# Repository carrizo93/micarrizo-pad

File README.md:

# micarrizo pad
 A macropad made using the Kailh Big Switch.

PCB front view:

PCB back view:

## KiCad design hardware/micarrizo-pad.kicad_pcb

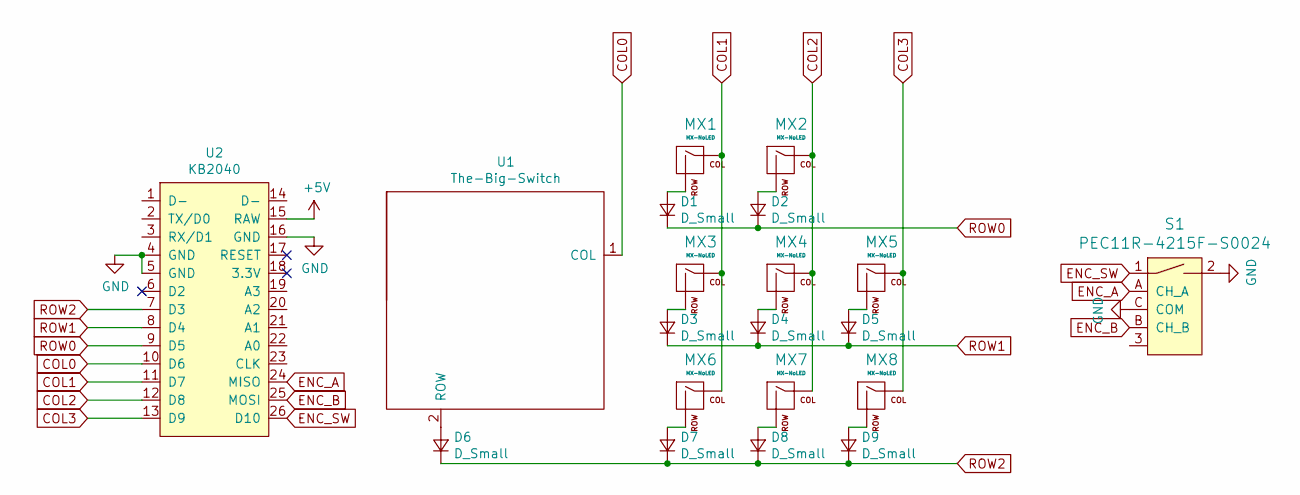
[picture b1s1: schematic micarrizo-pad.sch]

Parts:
D1, D2, D3, D4, D5, D6, D7, D8, D9: D_Small; D_SOD-123
MX1, MX2, MX3, MX4, MX5, MX6, MX7, MX8: MX-NoLED; MX-1U-NoLED
S1: PEC11R-4215F-S0024; Rotary_Encoder_Switched_PEC11R; MPN PEC11R-4215F-S0024; Digi-Key_PN PEC11R-4215F-S0024-ND
U1: The-Big-Switch; The Big Switch
U2: KB2040

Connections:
+5V: U2.15 (RAW)
COL0: U1.1 (COL), U2.10 (D6)
COL1: MX1.1 (COL), MX3.1 (COL), MX6.1 (COL), U2.11 (D7)
COL2: MX2.1 (COL), MX4.1 (COL), MX7.1 (COL), U2.12 (D8)
COL3: MX5.1 (COL), MX8.1 (COL), U2.13 (D9)
ENC_A: S1.A (CH_A), U2.24 (MISO)
ENC_B: S1.B (CH_B), U2.25 (MOSI)
ENC_SW: S1.1, U2.26 (D10)
GND: S1.2, S1.C (COM), U2.4 (GND), U2.5 (GND), U2.16 (GND)
unnamed: D1.2 (A), MX1.2 (ROW)
unnamed: D2.2 (A), MX2.2 (ROW)
unnamed: D3.2 (A), MX3.2 (ROW)
unnamed: D4.2 (A), MX4.2 (ROW)
unnamed: D5.2 (A), MX5.2 (ROW)
unnamed: D6.2 (A), U1.2 (ROW)
unnamed: D7.2 (A), MX6.2 (ROW)
unnamed: D8.2 (A), MX7.2 (ROW)
unnamed: D9.2 (A), MX8.2 (ROW)
ROW0: D1.1 (K), D2.1 (K), U2.9 (D5)
ROW1: D3.1 (K), D4.1 (K), D5.1 (K), U2.8 (D4)
ROW2: D6.1 (K), D7.1 (K), D8.1 (K), D9.1 (K), U2.7 (D3)

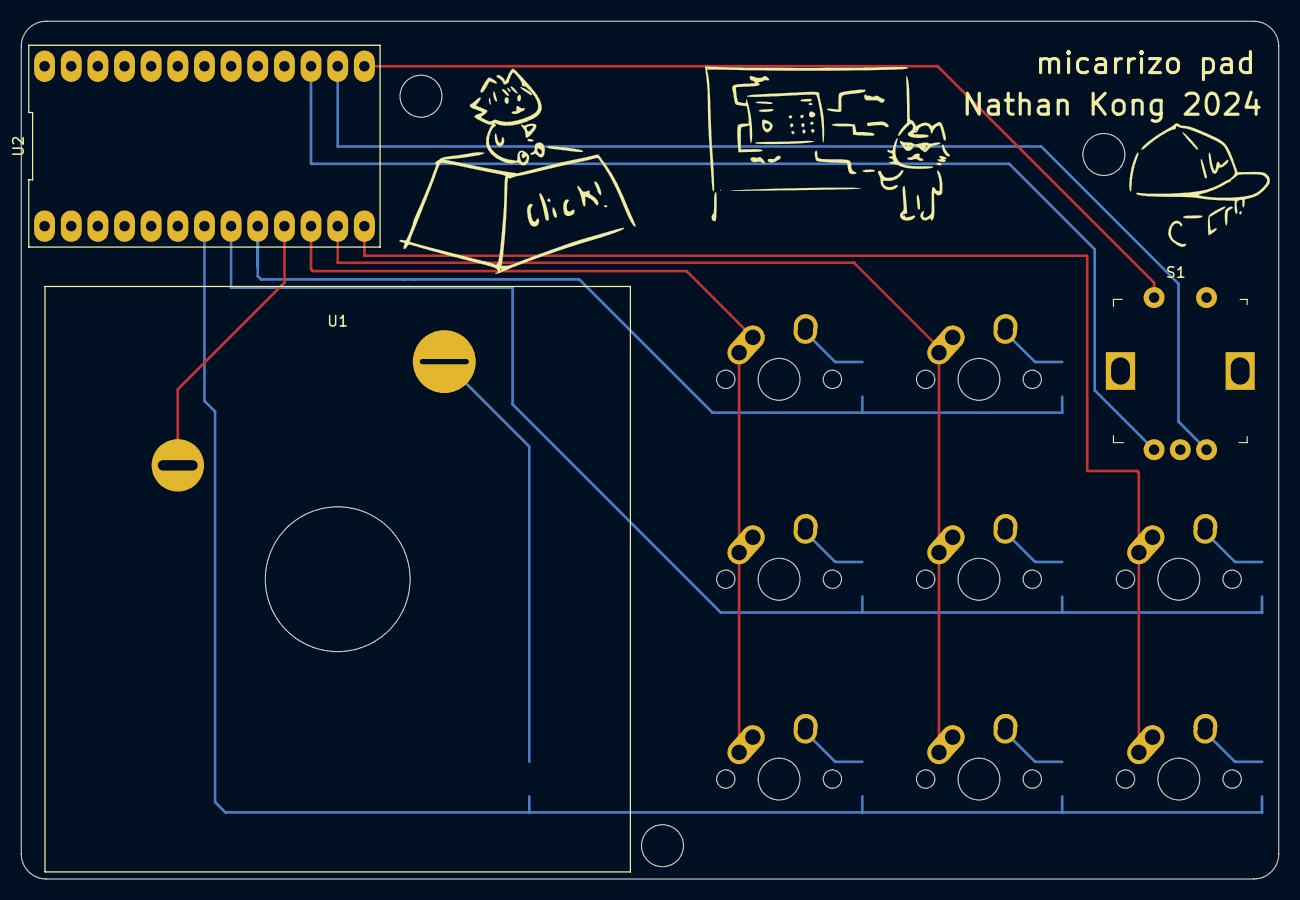
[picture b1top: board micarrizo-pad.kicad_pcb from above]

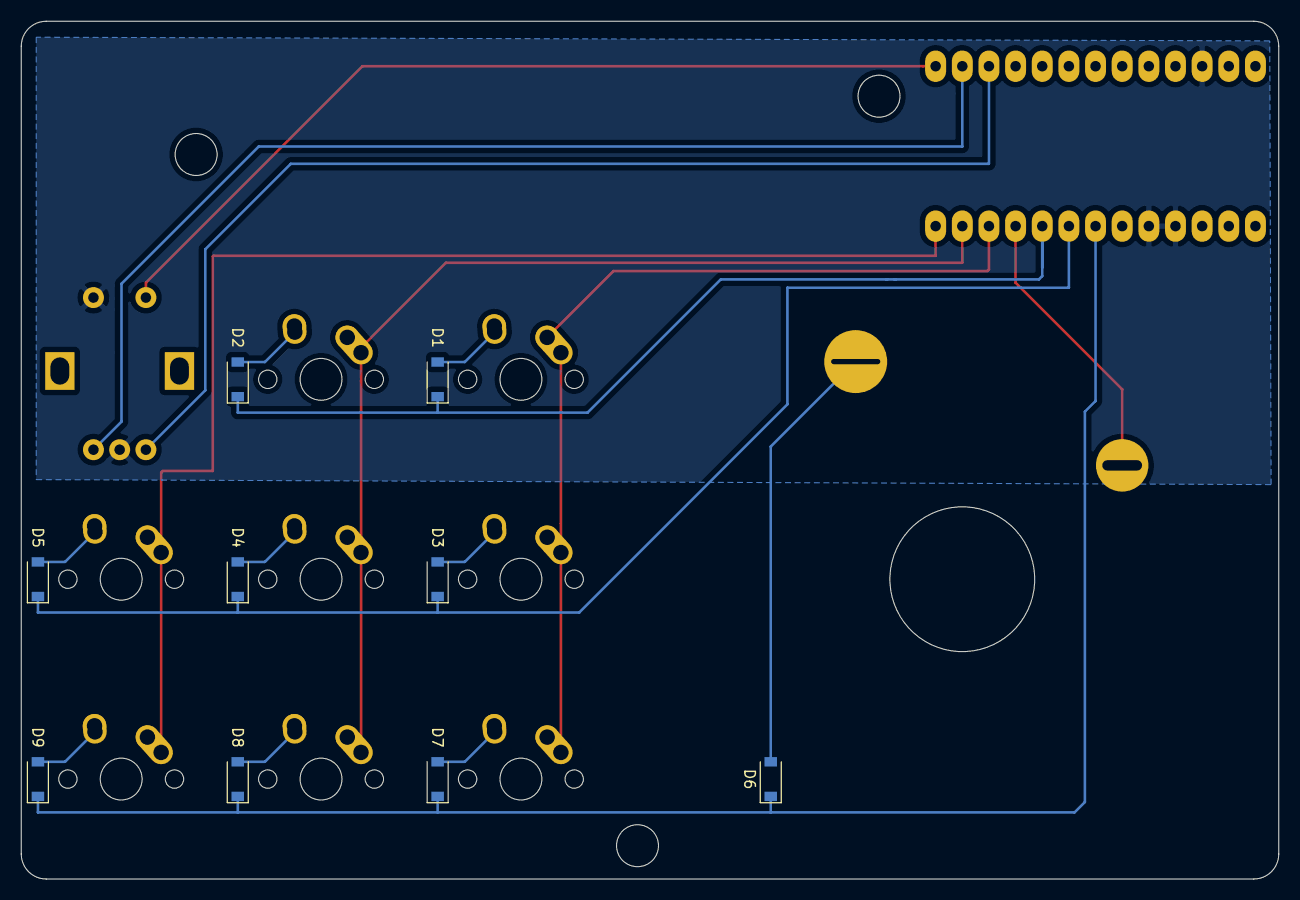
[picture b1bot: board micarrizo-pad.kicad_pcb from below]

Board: 2 copper layers, 119.9 x 81.8 mm, 20 parts (9 on the bottom side), 20 nets.

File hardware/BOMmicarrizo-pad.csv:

"Id";"Designator";"Package";"Quantity";"Designation";"Supplier and ref";
1;"G***";"meow";1;"LOGO";;;
2;"G***";"icon";1;"LOGO";;;
3;"U2";"KB2040";1;"KB2040";;;
4;"S1";"Rotary_Encoder_Switched_PEC11R";1;"PEC11R-4215F-S0024";;;
5;"U1";"The Big Switch";1;"The-Big-Switch";;;
6;"MX8,MX7,MX6,MX5,MX4,MX3,MX2,MX1";"MX-1U-NoLED";8;"MX-NoLED";;;
7;"D9,D8,D7,D6,D5,D4,D3,D2,D1";"D_SOD-123";9;"D_Small";;;

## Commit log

2024-02-17 Add submodules
2024-02-17 oops
2024-02-17 Add footprint libraries
2024-02-17 start macropad
2024-03-11 create big switch
2024-03-11 change big switch
2024-03-14 start footprint
2024-03-15 Add KB2040 submodule
2024-03-15 Add submodule
2024-03-15 add rows cols
2024-03-20 wire encoder
2024-03-21 start pcb
2024-03-21 finish pcb
2024-03-22 complete pcb add text
2024-03-22 reorganize project
2024-03-22 fix submodule
2024-03-22 re add submodules
2024-03-22 finish reorganizing
2024-03-25 generate bom and start code
2024-05-06 add screw holes, create gerbers
2024-05-27 set up encoder and keys
2024-06-16 add images
2024-06-16 add text
